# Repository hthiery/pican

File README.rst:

PICAN
=====

An interface card for connection the CAN bus to the rasperry pi.

This repository includes a Kicad design to build a PCB described at:

http://www.ifoedit.com/RaspiCS2En.html (english version)

http://www.ifoedit.com/RaspiCS2.html (german version)

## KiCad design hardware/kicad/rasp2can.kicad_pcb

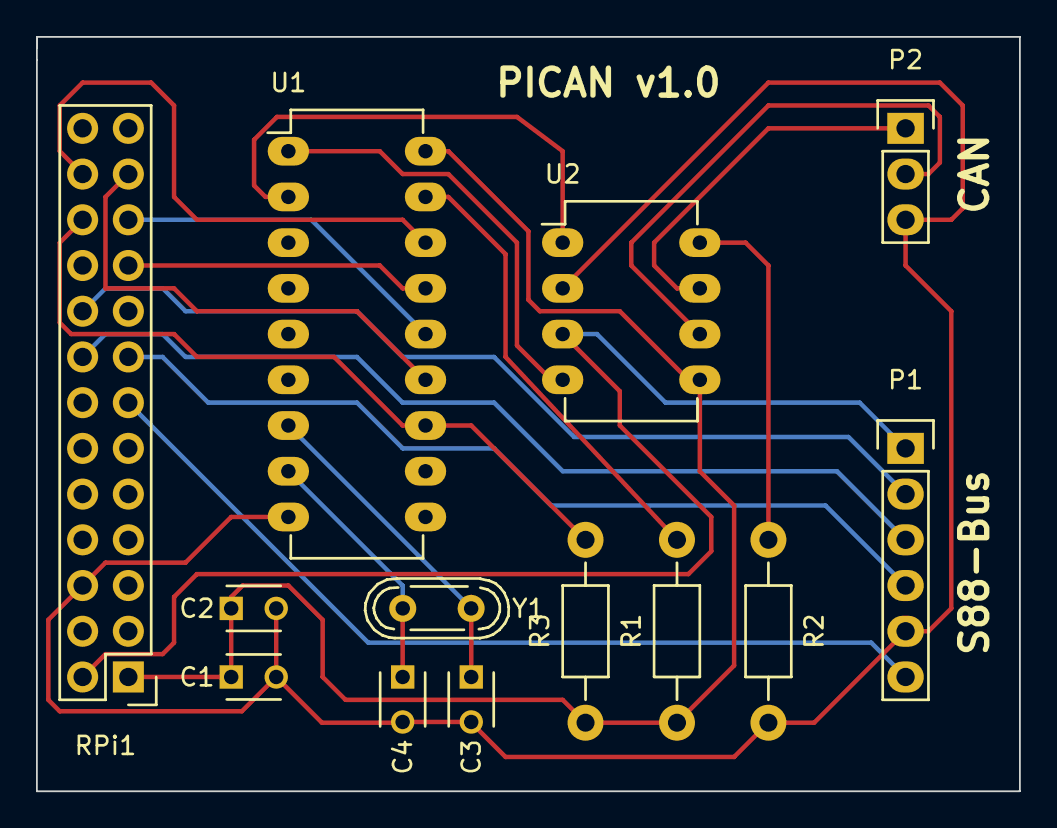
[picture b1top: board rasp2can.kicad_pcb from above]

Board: 2 copper layers, 54.6 x 41.9 mm, 13 parts (0 on the bottom side), 20 nets.

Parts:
C1, C2: 100nF; C_Disc_D3_P2.5
C3, C4: 22pF; C_Disc_D3_P2.5
P1: CONN_01X06; Pin_Header_Straight_1x06
P2: CONN_01X03; Pin_Header_Straight_1x03
R1: 4k7; Resistor_Horizontal_RM10mm
R2: R; Resistor_Horizontal_RM10mm
R3: 18k; Resistor_Horizontal_RM10mm
RPi1: RASPBERRY_IO; Pin_Header_Straight_2x13
U1: MCP2515; DIP-18_W7.62mm_LongPads
U2: MCP2562; DIP-8_W7.62mm_LongPads
Y1: 16MHz; Crystal_HC52-U_Vertical

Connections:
+3V3: C1.1, C2.1, R1.1, R3.2, RPi1.1, U1.18, U2.5
+5V: P1.1, RPi1.2, U2.3
/S88_CLOCK: P1.4, RPi1.15
/S88_DATA: P1.6, RPi1.13
/S88_PS: P1.3, RPi1.16
/S88_RESET: P1.2, RPi1.18
/SPI_CLK: RPi1.23, U1.13
/SPI_CS: RPi1.24, U1.16
/SPI_MISO: RPi1.19, U1.15
/SPI_MOSI: RPi1.21, U1.14
GND: C1.2, C2.2, C3.2, C4.2, P1.5, P2.3, R2.2, RPi1.6, U1.9, U2.2
unnamed: C3.1, U1.7, Y1.1
unnamed: C4.1, U1.8, Y1.2
unnamed: P2.1, U2.7
unnamed: P2.2, U2.6
unnamed: R1.2, U1.17
unnamed: R2.1, U2.8
unnamed: R3.1, RPi1.22, U1.12
unnamed: U1.1, U2.4
unnamed: U1.2, U2.1

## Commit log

2016-01-14 move kicad stuff to subfolder
2016-01-14 move file to hardware subfolder
2016-01-14 update hardware
2016-01-15 routing optimization
2016-01-15 add .gitignore
2016-01-15 add README.rst
2016-01-15 rename file to pican*
2016-01-15 update gerber files
2016-01-18 Add optocoupler and started new PCB.
2016-01-18 add new device LTV-847
2016-01-18 update schematic pdf
2016-01-18 change resistor values for optocoupler
